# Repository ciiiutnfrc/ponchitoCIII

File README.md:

# Poncho para Arduino UNO – ponchitoCIII

Este repositorio contiene el diseño de una la placa que cuenta con el hardware necesario para realizar las primeras prácticas en programación sobre sistemas embebidos. Se puede utilizar para el desarrollo de software con los esquemas de sketch de Arduino (con placas Arduino UNO o equivalente), programación en lenguaje C de los microcontroladores AVR de las placas Arduino (sin el IDE Arduino).

<!--
Una descripción más detallada se presenta en [Poncho para Arduino/Galileo – ponchitoCIII](https://github.com/ciiiutnfrc/ponchitoCIII/blob/master/doc/ponchito.pdf).
-->

Una descripción más detallada se presenta en [ponchitoCIII](doc/PonchitoCIII.md).

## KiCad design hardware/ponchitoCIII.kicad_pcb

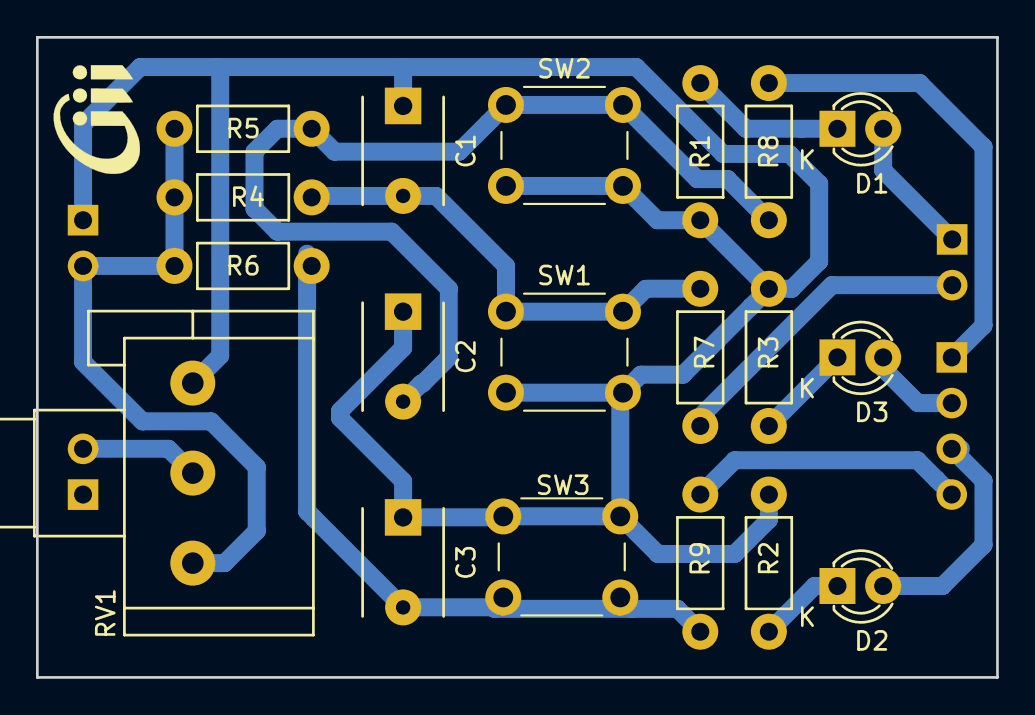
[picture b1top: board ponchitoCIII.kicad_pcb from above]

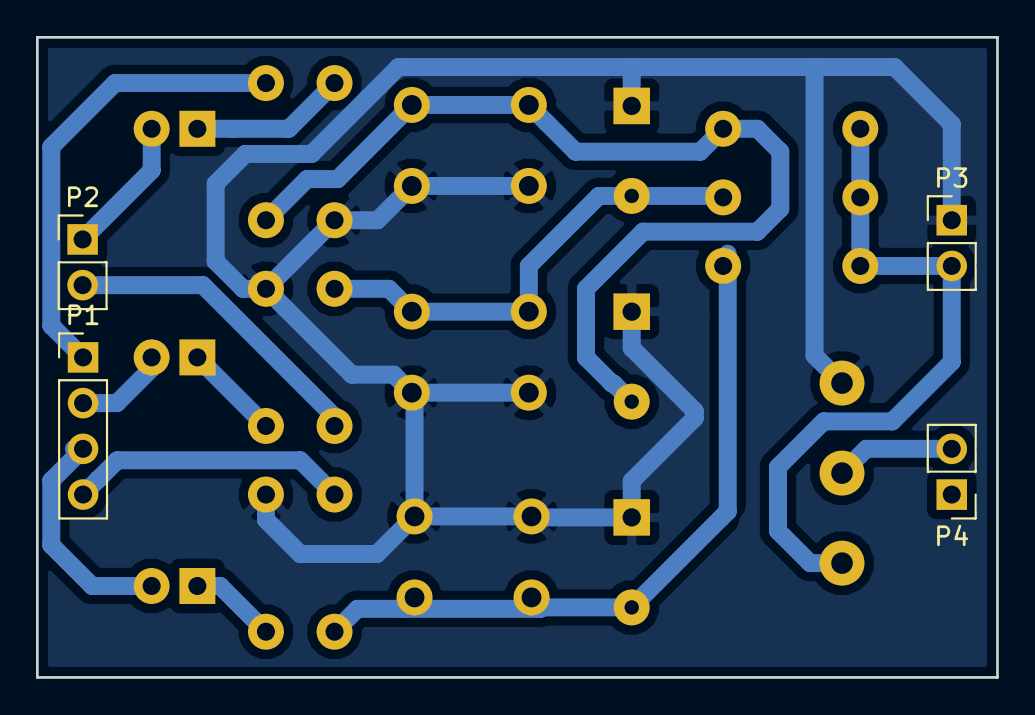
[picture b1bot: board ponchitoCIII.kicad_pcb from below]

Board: 2 copper layers, 53.3 x 35.6 mm, 24 parts (4 on the bottom side), 15 nets.

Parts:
C1, C2, C3: 100n; C_Disc_D6_P5
D1: rojo; LED-3MM-Red
D2: amarillo; LED-3MM-Yellow
D3: verde; LED-5MM-Green
Logo_1: Logo_CIII; Logo_CIII_Tiny_FSilk
P1: CONN_01X04; PinHeader_1x04_P2.54mm_Vertical
P2, P3, P4: CONN_01X02; PinHeader_1x02_P2.54mm_Vertical
R1, R2, R3, R7, R8, R9: 1K; Resistor_Horizontal_RM7mm
R4, R5, R6: 10K; Resistor_Horizontal_RM7mm
RV1: 5K; Potentiometer_Alps-RK16-single
SW1: izquierdo; SW_PUSH_6mm
SW2: centro; SW_PUSH_6mm
SW3: derecho; SW_PUSH_6mm

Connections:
GND: C1.1, C2.1, C3.1, P3.1, R1.1, R2.1, R3.1, RV1.3, SW1.2, SW2.2, SW3.2
unnamed: C1.2, R4.2, R7.1, SW1.1
unnamed: C2.2, R5.2, R8.1, SW2.1
unnamed: C3.2, R6.2, R9.1, SW3.1
unnamed: D1.1, R1.2
unnamed: D1.2, P2.1
unnamed: D2.1, R2.2
unnamed: D2.2, P1.3
unnamed: D3.1, R3.2
unnamed: D3.2, P1.2
unnamed: P1.1, R8.2
unnamed: P1.4, R9.2
unnamed: P2.2, R7.2
unnamed: P3.2, R4.1, R5.1, R6.1, RV1.1
unnamed: P4.2, RV1.2

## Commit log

2017-12-01 Sketch Arduino para probar el ponchito
2017-12-01 Documento LaTeX explicativo del ponchito.
2018-04-26 Se agregaron hipervínculos al documento explicativo del ponchito.
2018-04-26 Se renombraron los sketch de estado de botones por puerto serie.
2018-09-07 Actualización del documento del ponchito. Agregado de documento explicativo de los sketch de Arduino.
2018-09-07 Agregado de directorio 'hardware' con el diseño esquemático y PCB (KiCAD 5.0)
2019-05-27 Modificado archivo README
2019-05-27 Agregado archivo README del directorio 'sketch'
2020-08-03 Cambia constantes simbólica de sketchs
    - Se cambiaron las constantes simbólicas de GPIO_* a PIN_* (estido
    Arduino)
    - Se borraron algunas líneas en blanco de los sketchs
2025-02-17 Agrega documentación
2025-02-17 Actualiza README
